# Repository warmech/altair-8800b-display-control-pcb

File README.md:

# Altair 8800B Display/Control PCB
This is a reproduction of the Altair 8800B Display/Control PCB, with some cleanup and reorganization of trace routing and pad placement. The 8800B’s D/C PCB, much like the original 8800’s front panel PCB, is the primary form of I/O for a stock machine: the LEDs for indicating the data/address/control signals and switches for setting the address and inputting data as well as controlling the CPU are to be found on this PCB. Unlike the original 8800, which drove the LEDs directly off the system bus, the 8800B D/C PCB buffers all signals and uses a 1702 EPROM (or just “PROM” as it would have originally been called) to pass control instructions off to the CPU.

This version of the D/C PCB is not a true 1:1 reproduction (just like the 8800B CPU and Interface cards), but strives to maintain a closely similar layout and trace routing to try to ensure that the hidden “feature” of the Altair remained present: the ability to generate EMI off the D/C board in such a fashion that music can be generated and received via an AM radio at very close proximity.

This design is presently untested and I am awaiting a set to be fabricated. Once I have tested this card in my 8800B, I will update this disclaimer to indicate as much. Until this disclaimer is updated and/or removed, this PCB is to be strictly treated as experimental only. User beware – these project and fabrication files are provided with absolutely zero guarantees.

For the accompanying CPU, Interface, and 1702-to-2716/32 adapter boards, please see the following repositories:

[Altair 8800B CPU Card](https://github.com/warmech/altair-8800b-cpu-card)

[Altair 8800B Interface Card](https://github.com/warmech/altair-8800b-interface-card)

[Altair 8800B 1702-to-2716/2732 Adapter](https://github.com/warmech/altair-8800b-1702-to-2716-eprom-adapter)

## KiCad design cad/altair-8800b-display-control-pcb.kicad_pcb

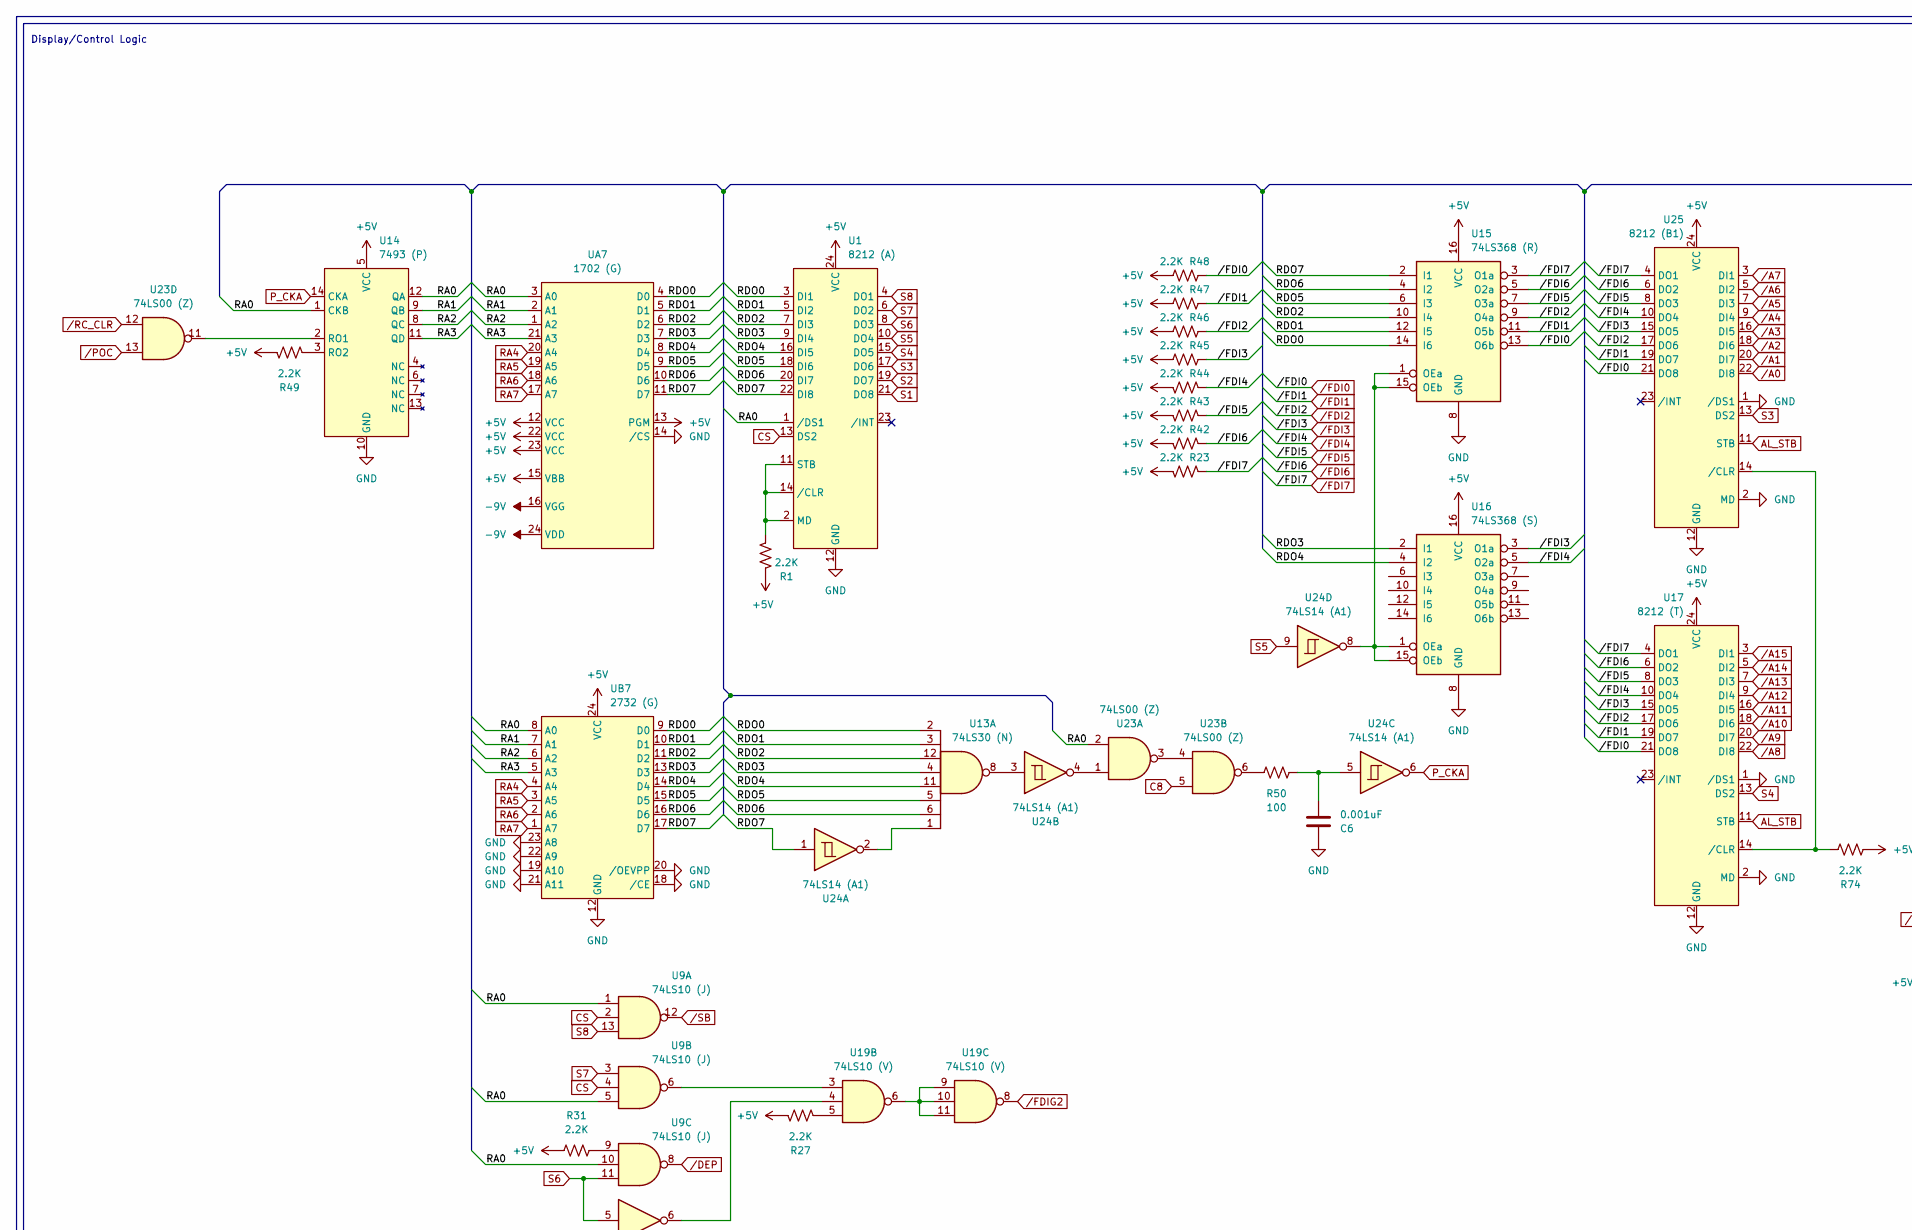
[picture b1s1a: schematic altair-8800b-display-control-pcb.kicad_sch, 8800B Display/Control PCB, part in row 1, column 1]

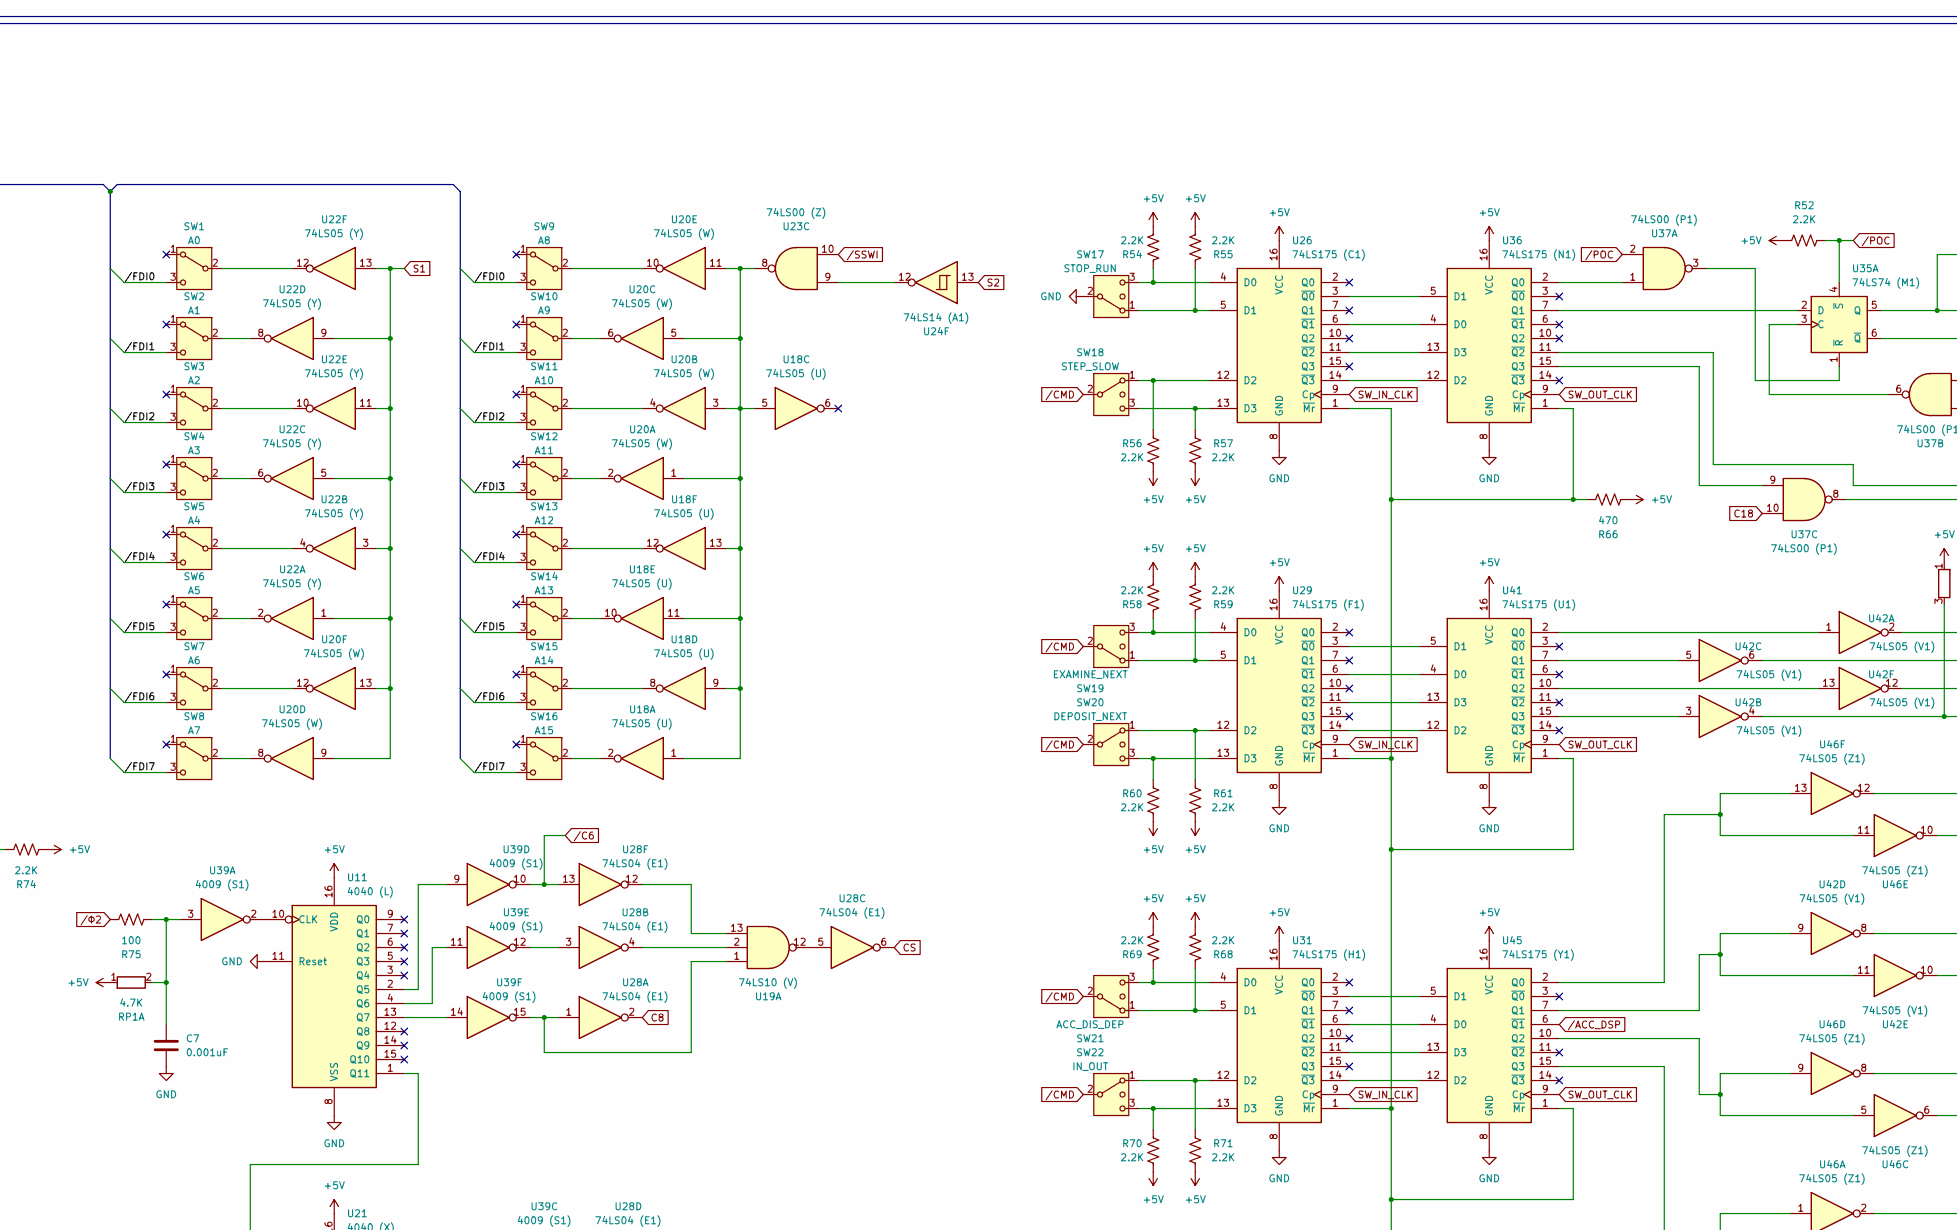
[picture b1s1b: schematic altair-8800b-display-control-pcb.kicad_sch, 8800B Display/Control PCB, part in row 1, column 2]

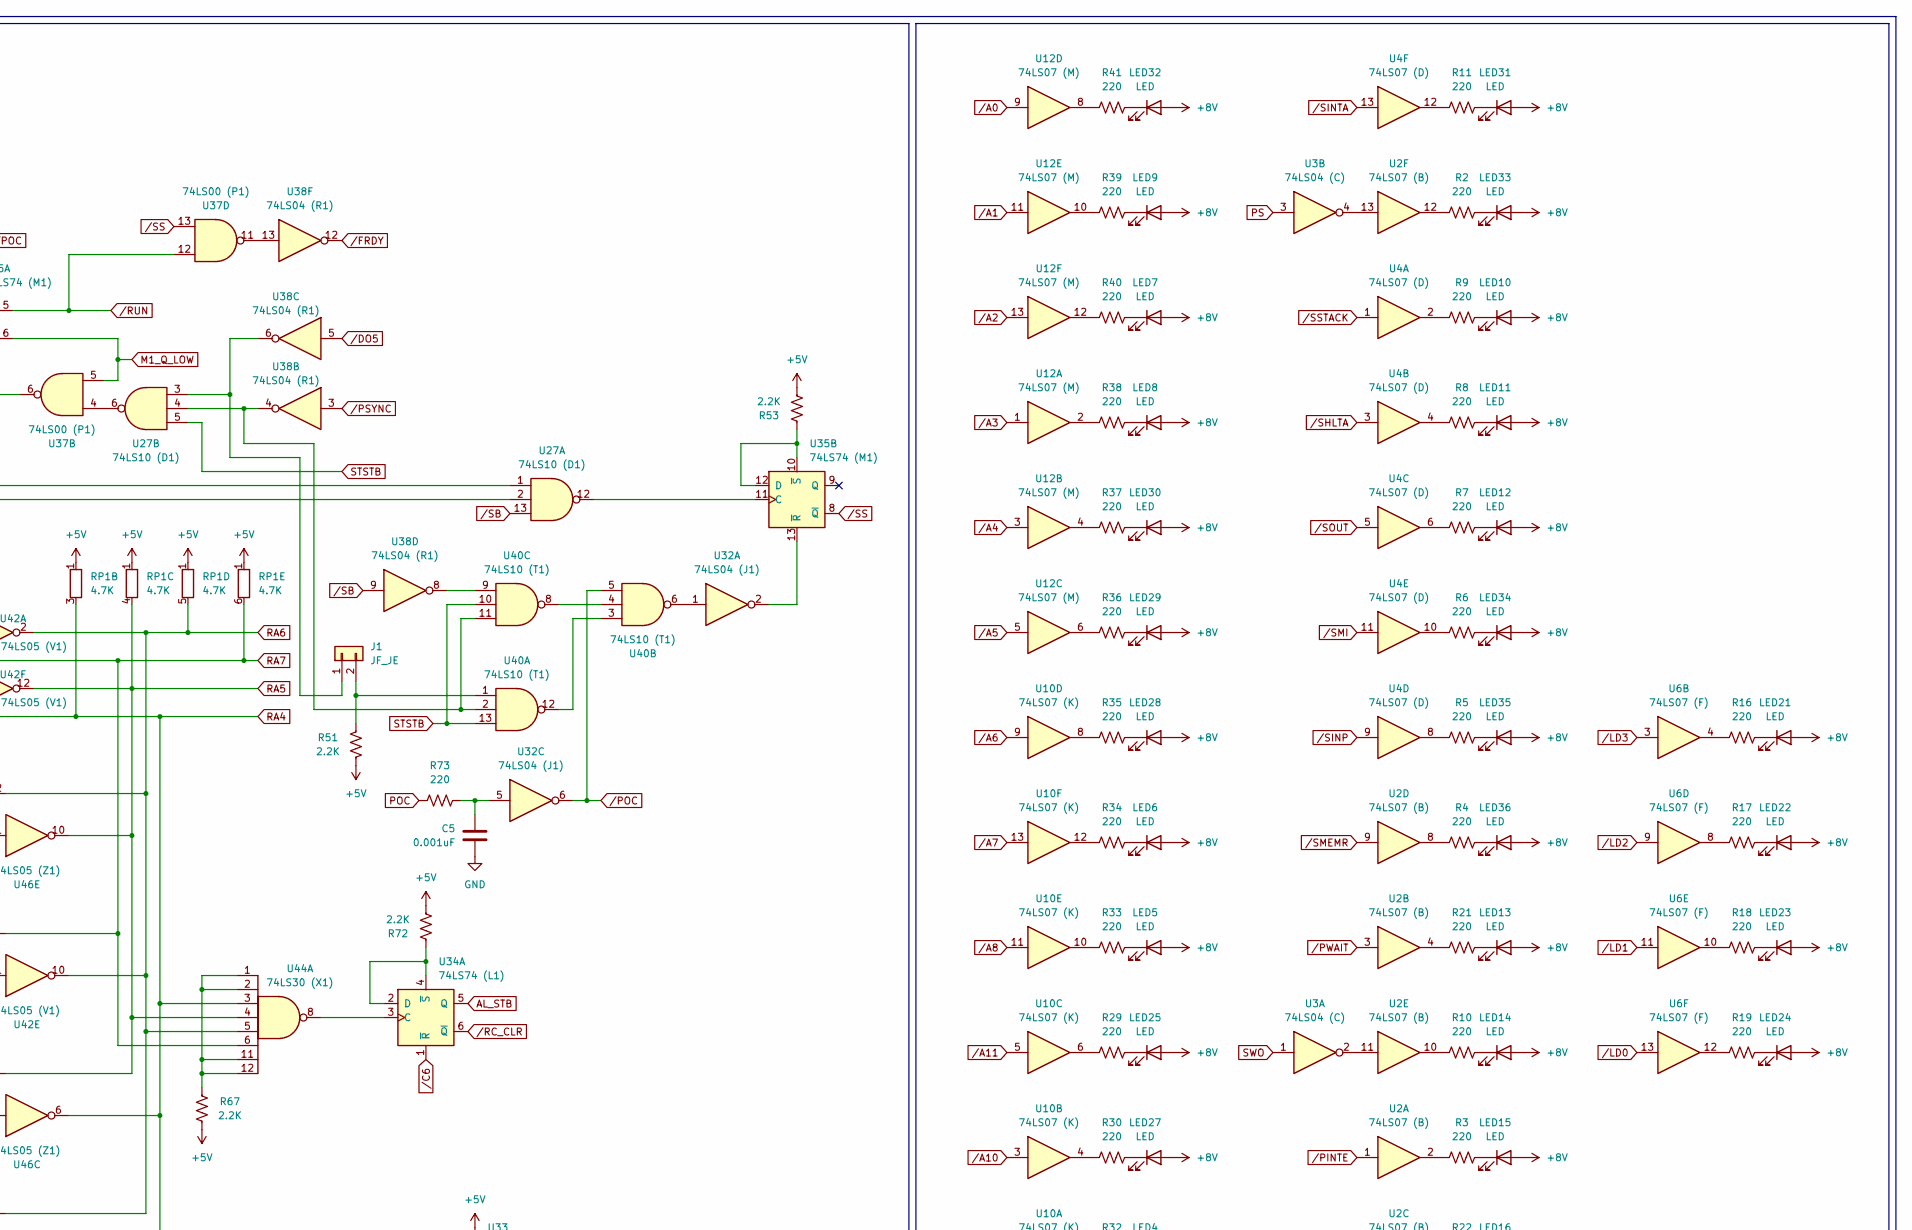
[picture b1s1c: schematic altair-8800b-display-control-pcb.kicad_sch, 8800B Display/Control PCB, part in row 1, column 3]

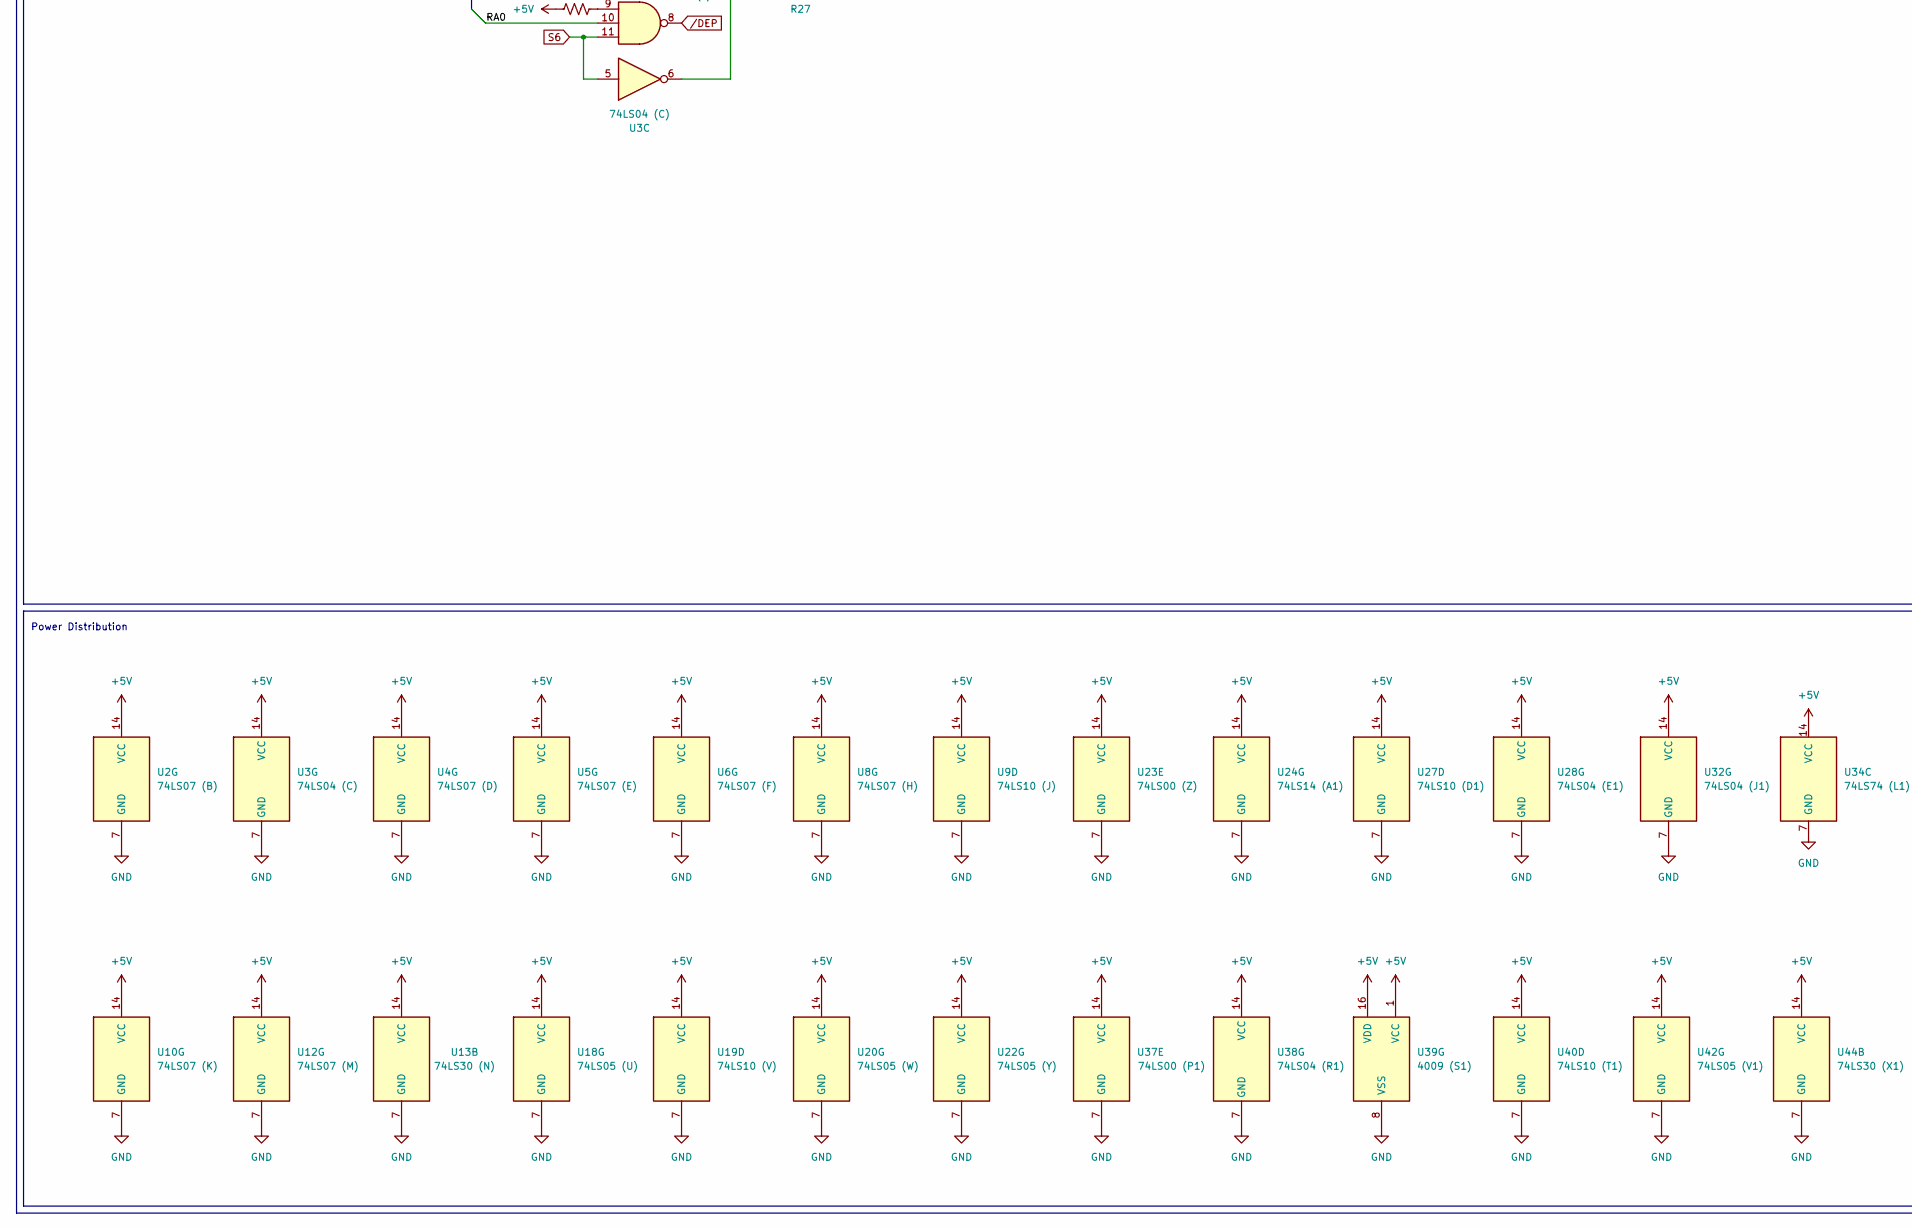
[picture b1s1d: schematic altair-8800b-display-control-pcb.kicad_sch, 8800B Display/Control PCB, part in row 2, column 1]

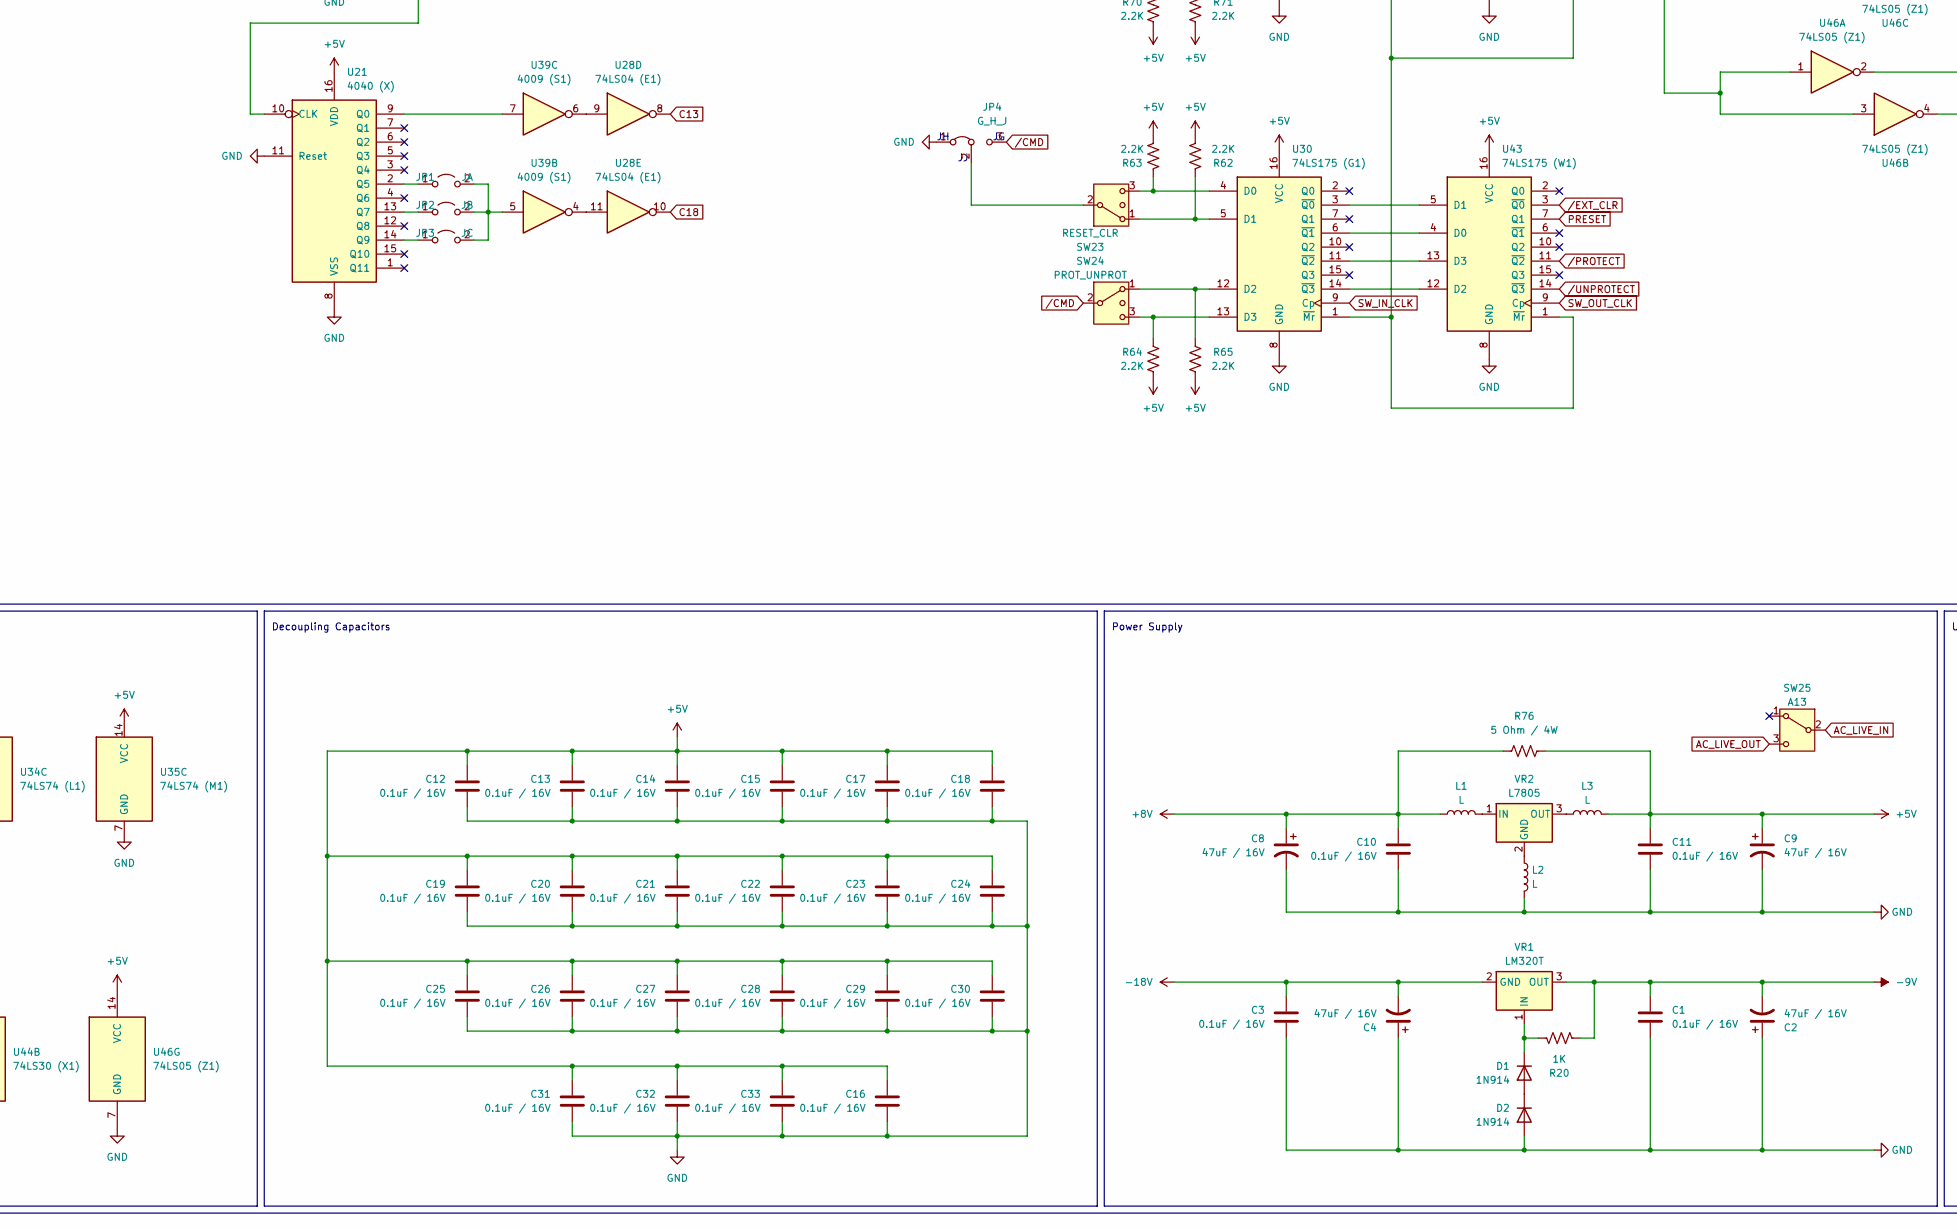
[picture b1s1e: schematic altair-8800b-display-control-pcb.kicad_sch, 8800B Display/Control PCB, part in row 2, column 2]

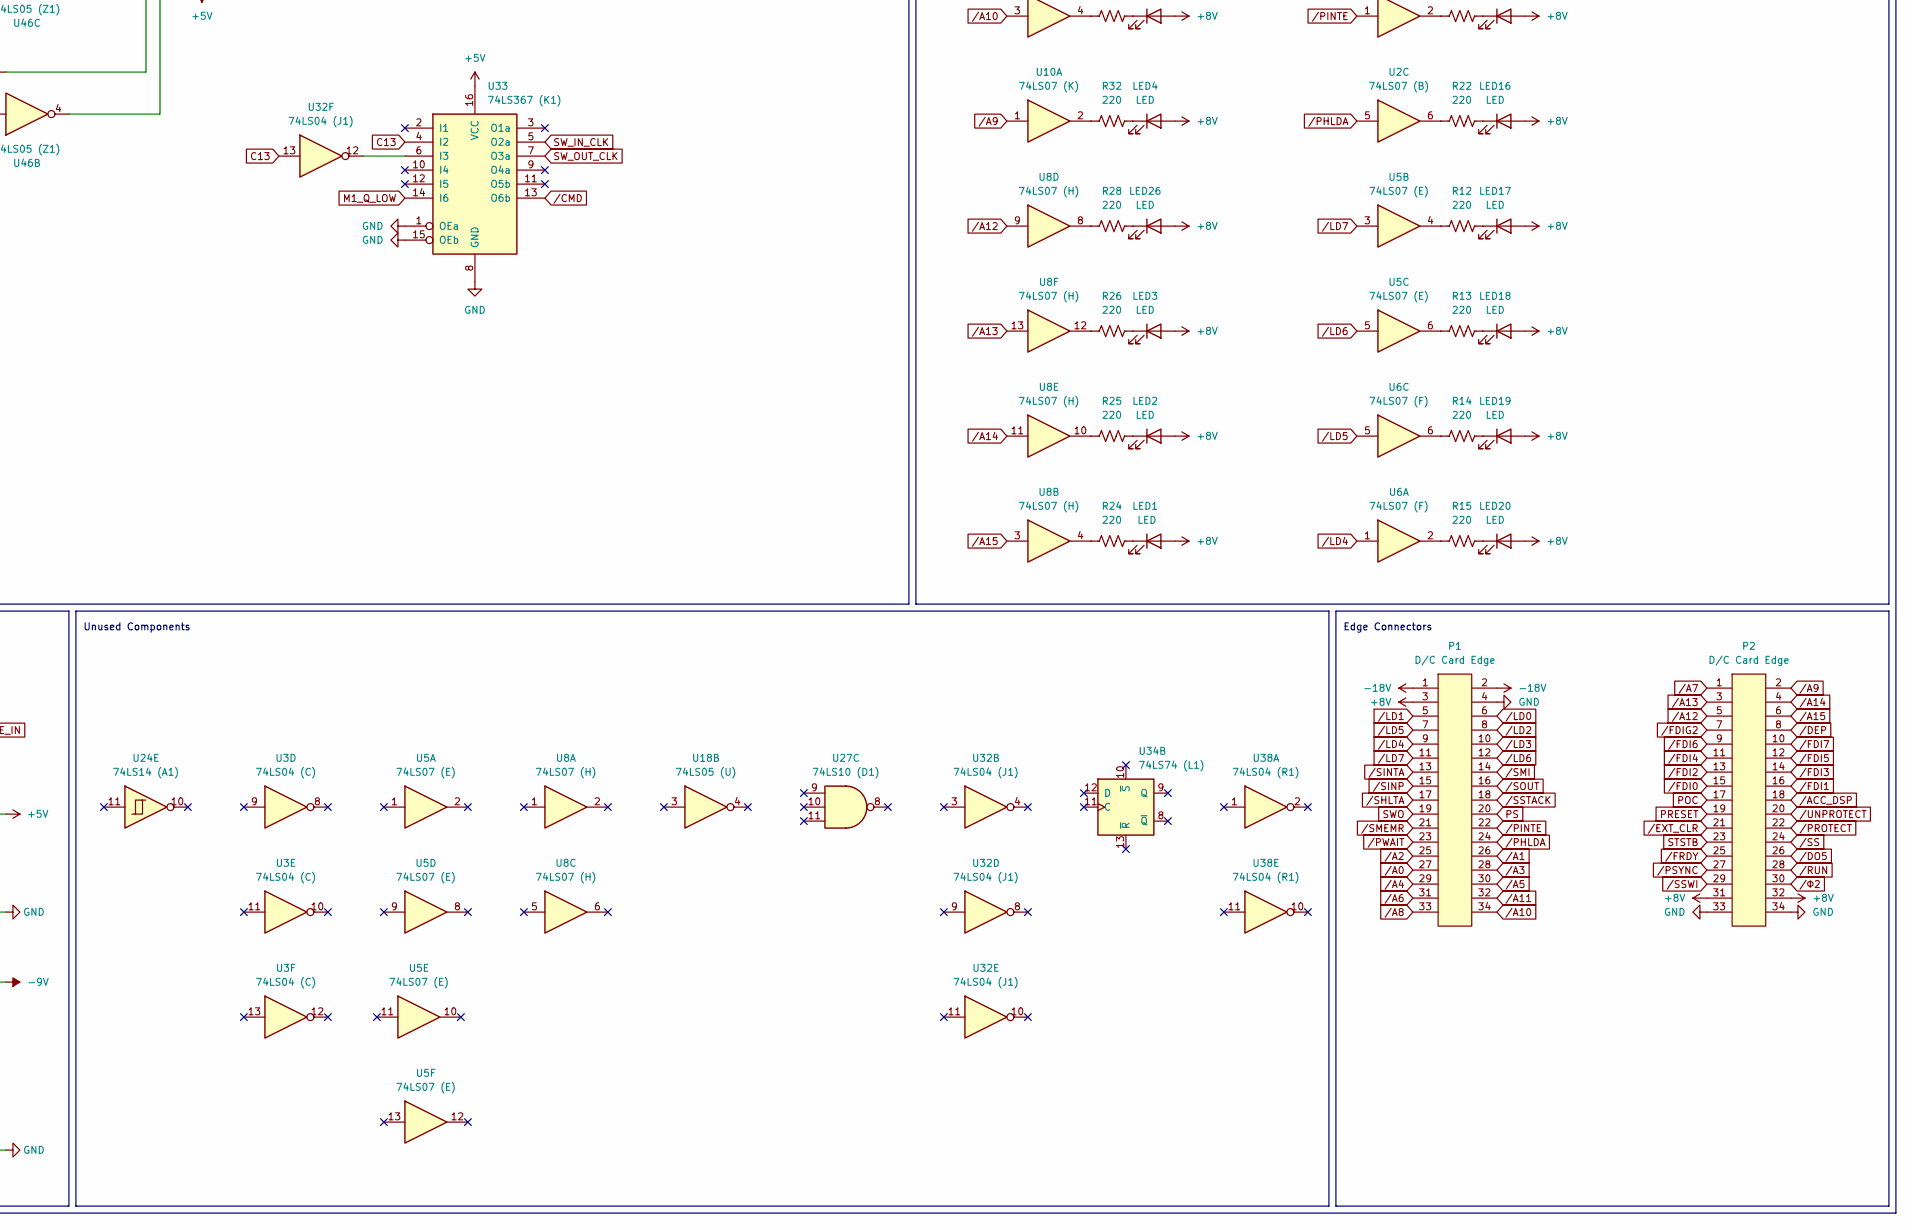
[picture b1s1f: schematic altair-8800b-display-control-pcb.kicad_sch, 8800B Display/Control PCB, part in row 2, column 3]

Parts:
C1, C3, C10, C11, C12, C13, C14, C15, C16, C17, C18, C19, C20, C21, C22, C23, C24, C25, C26, C27, C28, C29, C30, C31, C32, C33: 0.1uF / 16V; C_Disc_D7.0mm_W2.3mm_P5.00mm
C2, C4, C8, C9: 47uF / 16V; CP_Radial_Tantal_D4.5mm_P2.50mm
C5, C6, C7: 0.001uF; C_Disc_D7.0mm_W2.3mm_P5.00mm
D1, D2: 1N914; D_DO-35_SOD27_P7.62mm_Horizontal
J1: JF_JE; PinHeader_1x02_P2.54mm_Vertical
JP1: JA; PinHeader_1x02_P2.54mm_Vertical
JP2: JB; PinHeader_1x02_P2.54mm_Vertical
JP3: JC; PinHeader_1x02_P2.54mm_Vertical
JP4: G_H_J; PinHeader_1x03_P2.54mm_Vertical
L1, L2, L3: L; L_Axial_L5.3mm_D2.2mm_P7.62mm_Horizontal_Vishay_IM-1
LED1, LED2, LED3, LED4, LED5, LED6, LED7, LED8, LED9, LED10, LED11, LED12, LED13, LED14, LED15, LED16, LED17, LED18, LED19, LED20, LED21, LED22, LED23, LED24, LED25, LED26, LED27, LED28, LED29, LED30, LED31, LED32, LED33, LED34, LED35, LED36: LED; LED_D5.0mm
P1, P2: D/C Card Edge; Altair_8800B_Display_Control_Card_Edge
R1, R23, R27, R31, R42, R43, R44, R45, R46, R47, R48, R49, R51, R52, R53, R54, R55, R56, R57, R58, R59, R60, R61, R62, R63, R64, R65, R67, R68, R69, R70, R71, R72, R74: 2.2K; R_Axial_DIN0309_L9.0mm_D3.2mm_P12.70mm_Horizontal
R2, R3, R4, R5, R6, R7, R8, R9, R10, R11, R12, R13, R14, R15, R16, R17, R18, R19, R21, R22, R24, R25, R26, R28, R29, R30, R32, R33, R34, R35, R36, R37, R38, R39, R40, R41, R73: 220; R_Axial_DIN0309_L9.0mm_D3.2mm_P12.70mm_Horizontal
R20: 1K; R_Axial_DIN0309_L9.0mm_D3.2mm_P12.70mm_Horizontal
R50, R75: 100; R_Axial_DIN0309_L9.0mm_D3.2mm_P12.70mm_Horizontal
R66: 470; R_Axial_DIN0309_L9.0mm_D3.2mm_P12.70mm_Horizontal
R76: 5 Ohm / 4W; R_Axial_DIN0516_L15.5mm_D5.0mm_P30.48mm_Horizontal
RP1: 4.7K; R_Array_SIP6
SW1: A0; Altair_Toggle_Switch
SW2: A1; Altair_Toggle_Switch
SW3: A2; Altair_Toggle_Switch
SW4: A3; Altair_Toggle_Switch
SW5: A4; Altair_Toggle_Switch
SW6: A5; Altair_Toggle_Switch
SW7: A6; Altair_Toggle_Switch
SW8: A7; Altair_Toggle_Switch
SW9: A8; Altair_Toggle_Switch
SW10: A9; Altair_Toggle_Switch
SW11: A10; Altair_Toggle_Switch
SW12: A11; Altair_Toggle_Switch
SW13: A12; Altair_Toggle_Switch
SW14, SW25: A13; Altair_Toggle_Switch
SW15: A14; Altair_Toggle_Switch
SW16: A15; Altair_Toggle_Switch
SW17: STOP_RUN; Altair_Toggle_Switch_Momentary
SW18: STEP_SLOW; Altair_Toggle_Switch_Momentary
SW19: EXAMINE_NEXT; Altair_Toggle_Switch_Momentary
SW20: DEPOSIT_NEXT; Altair_Toggle_Switch_Momentary
SW21: ACC_DIS_DEP; Altair_Toggle_Switch_Momentary
SW22: IN_OUT; Altair_Toggle_Switch_Momentary
SW23: RESET_CLR; Altair_Toggle_Switch_Momentary
SW24: PROT_UNPROT; Altair_Toggle_Switch_Momentary
U1: 8212 (A); DIP-24_W15.24mm_LongPads
U2: 74LS07 (B); DIP-14_W7.62mm_LongPads
U3: 74LS04 (C); DIP-14_W7.62mm_LongPads
U4: 74LS07 (D); DIP-14_W7.62mm_LongPads
U5: 74LS07 (E); DIP-14_W7.62mm_LongPads
U6: 74LS07 (F); DIP-14_W7.62mm_LongPads
U8: 74LS07 (H); DIP-14_W7.62mm_LongPads
U9: 74LS10 (J); DIP-14_W7.62mm_LongPads
U10: 74LS07 (K); DIP-14_W7.62mm_LongPads
U11: 4040 (L); DIP-16_W7.62mm_LongPads
U12: 74LS07 (M); DIP-14_W7.62mm_LongPads
U13: 74LS30 (N); DIP-14_W7.62mm_LongPads
U14: 7493 (P); DIP-14_W7.62mm_LongPads
U15: 74LS368 (R); DIP-16_W7.62mm_LongPads
U16: 74LS368 (S); DIP-16_W7.62mm_LongPads
U17: 8212 (T); DIP-24_W15.24mm_LongPads
U18: 74LS05 (U); DIP-14_W7.62mm_LongPads
U19: 74LS10 (V); DIP-14_W7.62mm_LongPads
U20: 74LS05 (W); DIP-14_W7.62mm_LongPads
U21: 4040 (X); DIP-16_W7.62mm_LongPads
U22: 74LS05 (Y); DIP-14_W7.62mm_LongPads
U23: 74LS00 (Z); DIP-14_W7.62mm_LongPads
U24: 74LS14 (A1); DIP-14_W7.62mm_LongPads
U25: 8212 (B1); DIP-24_W15.24mm_LongPads
U26: 74LS175 (C1); DIP-16_W7.62mm_LongPads
U27: 74LS10 (D1); DIP-14_W7.62mm_LongPads
U28: 74LS04 (E1); DIP-14_W7.62mm_LongPads
U29: 74LS175 (F1); DIP-16_W7.62mm_LongPads
U30: 74LS175 (G1); DIP-16_W7.62mm_LongPads
U31: 74LS175 (H1); DIP-16_W7.62mm_LongPads
U32: 74LS04 (J1); DIP-14_W7.62mm_LongPads
U33: 74LS367 (K1); DIP-16_W7.62mm_LongPads
U34: 74LS74 (L1); DIP-14_W7.62mm_LongPads
U35: 74LS74 (M1); DIP-14_W7.62mm_LongPads
U36: 74LS175 (N1); DIP-16_W7.62mm_LongPads
U37: 74LS00 (P1); DIP-14_W7.62mm_LongPads
U38: 74LS04 (R1); DIP-14_W7.62mm_LongPads
U39: 4009 (S1); DIP-16_W7.62mm_LongPads
U40: 74LS10 (T1); DIP-14_W7.62mm_LongPads
U41: 74LS175 (U1); DIP-16_W7.62mm_LongPads
U42: 74LS05 (V1); DIP-14_W7.62mm_LongPads
U43: 74LS175 (W1); DIP-16_W7.62mm_LongPads
U44: 74LS30 (X1); DIP-14_W7.62mm_LongPads
U45: 74LS175 (Y1); DIP-16_W7.62mm_LongPads
U46: 74LS05 (Z1); DIP-14_W7.62mm_LongPads
UA7: 1702 (G); DIP-24_W15.24mm_LongPads
UB7: 2732 (G)
VR1: LM320T; TO-220-3_Horizontal_TabDown
VR2: L7805; TO-220-3_Horizontal_TabDown

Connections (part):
+5V: C9.1, C11.1, C12.1, C13.1, C14.1, C15.1, C16.1, C17.1, C18.1, C19.1, C20.1, C21.1, C22.1, C23.1, C24.1, C25.1, C26.1, C27.1, C28.1, C29.1, C30.1, C31.1, C32.1, C33.1, L3.2, R1.1, R23.1, R27.1, R31.1, R42.1, R43.1, R44.1, R45.2, R46.2, R47.2, R48.2, R49.1, R51.2, R52.1, R53.2, R54.1, R55.2, R56.1, R57.2, R58.1, R59.2, R60.1, R61.2, R62.2, R63.1, R64.1, R65.2, R66.1, R67.2, R68.2, R69.1, R70.1, R71.2, R72.2, R74.1, R76.2, RP1.1 (R1), U1.24 (VCC), U2.14 (VCC), U3.14 (VCC), U4.14 (VCC), U5.14 (VCC), U6.14 (VCC), U8.14 (VCC), U9.14 (VCC), U10.14 (VCC), U11.16 (VDD), U12.14 (VCC), U13.14 (VCC), U14.5 (VCC), U15.16 (VCC), U16.16 (VCC), U17.24 (VCC), U18.14 (VCC), U19.14 (VCC), U20.14 (VCC), U21.16 (VDD), U22.14 (VCC)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
+8V: C8.1, C10.1, L1.1, LED1.2 (A), LED2.2 (A), LED3.2 (A), LED4.2 (A), LED5.2 (A), LED6.2 (A), LED7.2 (A), LED8.2 (A), LED9.2 (A), LED10.2 (A), LED11.2 (A), LED12.2 (A), LED13.2 (A), LED14.2 (A), LED15.2 (A), LED16.2 (A), LED17.2 (A), LED18.2 (A), LED19.2 (A), LED20.2 (A), LED21.2 (A), LED22.2 (A), LED23.2 (A), LED24.2 (A), LED25.2 (A), LED26.2 (A), LED27.2 (A), LED28.2 (A), LED29.2 (A), LED30.2 (A), LED31.2 (A), LED32.2 (A), LED33.2 (A), LED34.2 (A), LED35.2 (A), LED36.2 (A), P1.3, P2.31, P2.32, R76.1
-9V: C1.1, C2.2, R20.2, UA7.16 (VGG), UA7.24 (VDD), VR1.3 (OUT)
-18V: C3.1, C4.2, P1.1, P1.2, VR1.2 (GND)
/RA0: U1.1 (/DS1), U9.1, U9.5, U9.10, U14.1 (CKB), U14.12 (QA), U23.2, UA7.3 (A0), UB7.8 (A0)
/RA1: U14.9 (QB), UA7.2 (A1), UB7.7 (A1)
/RA2: U14.8 (QC), UA7.1 (A2), UB7.6 (A2)
/RA3: U14.11 (QD), UA7.21 (A3), UB7.5 (A3)
/RDO0: U1.3 (DI1), U13.2, U15.14 (I6), UA7.4 (D0), UB7.9 (D0)
/RDO1: U1.5 (DI2), U13.3, U15.12 (I5), UA7.5 (D1), UB7.10 (D1)
/RDO2: U1.7 (DI3), U13.12, U15.10 (I4), UA7.6 (D2), UB7.11 (D2)
/RDO3: U1.9 (DI4), U13.4, U16.2 (I1), UA7.7 (D3), UB7.13 (D3)
/RDO4: U1.16 (DI5), U13.11, U16.4 (I2), UA7.8 (D4), UB7.14 (D4)
/RDO5: U1.18 (DI6), U13.5, U15.6 (I3), UA7.9 (D5), UB7.15 (D5)
/RDO6: U1.20 (DI7), U13.6, U15.4 (I2), UA7.10 (D6), UB7.16 (D6)
/RDO7: U1.22 (DI8), U15.2 (I1), U24.1, UA7.11 (D7), UB7.17 (D7)
AC_LIVE_IN: SW25.2 (B)
AC_LIVE_OUT: SW25.3 (C)
AL_STB: U17.11 (STB), U25.11 (STB), U34.5 (Q)
C8: U23.5, U28.2
C13: U28.8, U32.13, U33.4 (I2)
C18: U28.10, U37.10
CS: U1.13 (DS2), U9.2, U9.4, U28.6
GND: C1.2, C2.1, C3.2, C4.1, C5.1, C6.1, C7.1, C8.2, C9.2, C10.2, C11.2, C12.2, C13.2, C14.2, C15.2, C16.2, C17.2, C18.2, C19.2, C20.2, C21.2, C22.2, C23.2, C24.2, C25.2, C26.2, C27.2, C28.2, C29.2, C30.2, C31.2, C32.2, C33.2, D2.2 (A), JP4.1 (A), L2.2, P1.4, P2.33, P2.34, SW17.2 (3), U1.12 (GND), U2.7 (GND), U3.7 (GND), U4.7 (GND), U5.7 (GND), U6.7 (GND), U8.7 (GND), U9.7 (GND), U10.7 (GND), U11.8 (VSS), U11.11 (Reset), U12.7 (GND), U13.7 (GND), U14.10 (GND), U15.8 (GND), U16.8 (GND), U17.1 (/DS1), U17.2 (MD), U17.12 (GND), U18.7 (GND), U19.7 (GND), U20.7 (GND), U21.8 (VSS), U21.11 (Reset), U22.7 (GND), U23.7 (GND), U24.7 (GND), U25.1 (/DS1), U25.2 (MD), U25.12 (GND), U26.8 (GND), U27.7 (GND), U28.7 (GND), U29.8 (GND), U30.8 (GND), U31.8 (GND), U32.7 (GND), U33.1 (OEa), U33.8 (GND), U33.15 (OEb), U34.7 (GND), U35.7 (GND), U36.8 (GND)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
M1_Q_LOW: U33.14 (I6), U35.6 (~Q), U37.5
unnamed: C5.2, R73.2, U32.5
unnamed: C6.2, R50.2, U24.5
unnamed: D1.2 (A), D2.1 (K)
unnamed: D1.1 (K), R20.1, VR1.1 (IN)
unnamed: J1.1, U27.3, U38.6
unnamed: J1.2, R51.1, U40.1
unnamed: JP1.1 (A), U21.2 (Q5)
unnamed: JP1.2 (B), JP2.2 (B), JP3.2 (B), U39.5
unnamed: JP2.1 (A), U21.13 (Q7)
unnamed: JP3.1 (A), U21.14 (Q9)
unnamed: JP4.2 (C), SW23.2 (3)
unnamed: LED1.1 (K), R24.2
unnamed: LED2.1 (K), R25.2
unnamed: LED3.1 (K), R26.2
unnamed: LED4.1 (K), R32.2
unnamed: LED5.1 (K), R33.2
unnamed: LED6.1 (K), R34.2
unnamed: LED7.1 (K), R40.2
unnamed: LED8.1 (K), R38.2
unnamed: LED9.1 (K), R39.2
unnamed: LED10.1 (K), R9.2
unnamed: LED11.1 (K), R8.2
unnamed: LED12.1 (K), R7.2
unnamed: LED13.1 (K), R21.2
unnamed: LED14.1 (K), R10.2
unnamed: LED15.1 (K), R3.2
unnamed: LED16.1 (K), R22.2
unnamed: LED17.1 (K), R12.2
unnamed: LED18.1 (K), R13.2
unnamed: LED19.1 (K), R14.2
unnamed: LED20.1 (K), R15.2
unnamed: LED21.1 (K), R16.2
unnamed: LED22.1 (K), R17.2
unnamed: LED23.1 (K), R18.2
unnamed: LED24.1 (K), R19.2
unnamed: LED25.1 (K), R29.2
unnamed: LED26.1 (K), R28.2
unnamed: LED27.1 (K), R30.2
unnamed: LED28.1 (K), R35.2
unnamed: LED29.1 (K), R36.2
unnamed: LED30.1 (K), R37.2
unnamed: LED31.1 (K), R11.2
unnamed: LED32.1 (K), R41.2
unnamed: LED33.1 (K), R2.2
unnamed: LED34.1 (K), R6.2
unnamed: LED35.1 (K), R5.2
unnamed: LED36.1 (K), R4.2
unnamed: R2.1, U2.12
unnamed: R3.1, U2.2
unnamed: R4.1, U2.8
unnamed: R5.1, U4.8
unnamed: R6.1, U4.10
unnamed: R7.1, U4.6
unnamed: R8.1, U4.4
unnamed: R9.1, U4.2
unnamed: R10.1, U2.10
unnamed: R11.1, U4.12
unnamed: R12.1, U5.4
unnamed: R13.1, U5.6
unnamed: R14.1, U6.6
unnamed: R15.1, U6.2
unnamed: R16.1, U6.4
unnamed: R17.1, U6.8
unnamed: R18.1, U6.10
unnamed: R19.1, U6.12
unnamed: R21.1, U2.4
unnamed: R22.1, U2.6
unnamed: R24.1, U8.4
unnamed: R25.1, U8.10
unnamed: R26.1, U8.12
unnamed: R27.2, U19.5
unnamed: R28.1, U8.8
unnamed: R29.1, U10.6
unnamed: R30.1, U10.4
unnamed: R31.2, U9.9
unnamed: R32.1, U10.2
unnamed: R33.1, U10.10
unnamed: R34.1, U10.12
unnamed: R35.1, U10.8
unnamed: R36.1, U12.6
unnamed: R37.1, U12.4
unnamed: R38.1, U12.2
unnamed: R39.1, U12.10
unnamed: R40.1, U12.12
unnamed: R41.1, U12.8
unnamed: R50.1, U23.6
unnamed: R67.1, U44.1, U44.2, U44.11, U44.12
unnamed: C7.2, R75.1, RP1.2 (R1.2), U39.3
unnamed: SW1.2 (B), U22.12
unnamed: SW2.2 (B), U22.8
unnamed: SW3.2 (B), U22.10
unnamed: SW4.2 (B), U22.6
unnamed: SW5.2 (B), U22.4
unnamed: SW6.2 (B), U22.2
unnamed: SW7.2 (B), U20.12
unnamed: SW8.2 (B), U20.8
unnamed: SW9.2 (B), U20.10
unnamed: SW10.2 (B), U20.6
unnamed: SW11.2 (B), U20.4
unnamed: SW12.2 (B), U20.2
unnamed: SW13.2 (B), U18.12
unnamed: SW14.2 (B), U18.10
unnamed: SW15.2 (B), U18.8
unnamed: SW16.2 (B), U18.2
unnamed: R54.2, SW17.3 (4), U26.4 (D0)
unnamed: R57.1, SW18.3 (4), U26.13 (D3)
unnamed: R58.2, SW19.3 (4), U29.4 (D0)
unnamed: R60.2, SW20.3 (4), U29.13 (D3)
unnamed: R69.2, SW21.3 (4), U31.4 (D0)
unnamed: R70.2, SW22.3 (4), U31.13 (D3)
unnamed: R63.2, SW23.3 (4), U30.4 (D0)
unnamed: R64.2, SW24.3 (4), U30.13 (D3)
unnamed: R1.2, U1.2 (MD), U1.11 (STB), U1.14 (/CLR)
unnamed: U2.11, U3.2
unnamed: U2.13, U3.4
unnamed: U11.10 (CLK), U39.2
unnamed: U11.2 (Q5), U39.9
unnamed: U11.4 (Q6), U39.11
unnamed: U11.13 (Q7), U39.14
unnamed: U11.1 (Q11), U21.10 (CLK)
unnamed: U13.1, U24.2
unnamed: U13.8, U24.3
unnamed: U14.2 (RO1), U23.11
unnamed: R49.2, U14.3 (RO2)
unnamed: U15.1 (OEa), U15.15 (OEb), U16.1 (OEa), U16.15 (OEb), U24.8
unnamed: R74.2, U17.14 (/CLR), U25.14 (/CLR)
unnamed: U18.1, U18.5, U18.9, U18.11, U18.13, U20.1, U20.3, U20.5, U20.11, U23.8
unnamed: U19.1, U28.1, U39.15
unnamed: U19.2, U28.4
unnamed: U9.6, U19.3
unnamed: U3.6, U19.4
unnamed: U19.6, U19.9, U19.10, U19.11
unnamed: U19.12, U28.5
unnamed: U19.13, U28.12
unnamed: U21.9 (Q0), U39.7
unnamed: U23.1, U24.4
unnamed: U23.3, U23.4
unnamed: U23.9, U24.12
unnamed: R55.1, SW17.1, U26.5 (D1)
unnamed: R56.2, SW18.1, U26.12 (D2)
unnamed: R66.2, U26.1 (~Mr), U29.1 (~Mr), U30.1 (~Mr), U31.1 (~Mr), U36.1 (~Mr), U41.1 (~Mr), U43.1 (~Mr), U45.1 (~Mr)
unnamed: U26.3 (~Q0), U36.5 (D1)
unnamed: U26.6 (~Q1), U36.4 (D0)
unnamed: U26.11 (~Q2), U36.13 (D3)
unnamed: U26.14 (~Q3), U36.12 (D2)
unnamed: U27.2, U37.8
unnamed: U27.4, U38.4, U40.2, U40.11
unnamed: U27.6, U37.4
unnamed: U28.3, U39.12
unnamed: U28.9, U39.6
unnamed: U28.11, U39.4
unnamed: R59.1, SW19.1, U29.5 (D1)
unnamed: R61.1, SW20.1, U29.12 (D2)
unnamed: U29.3 (~Q0), U41.5 (D1)
unnamed: U29.6 (~Q1), U41.4 (D0)
unnamed: U29.11 (~Q2), U41.13 (D3)
unnamed: U29.14 (~Q3), U41.12 (D2)
unnamed: R62.1, SW23.1, U30.5 (D1)
unnamed: R65.1, SW24.1, U30.12 (D2)
unnamed: U30.3 (~Q0), U43.5 (D1)
unnamed: U30.6 (~Q1), U43.4 (D0)
unnamed: U30.11 (~Q2), U43.13 (D3)
unnamed: U30.14 (~Q3), U43.12 (D2)
unnamed: R68.1, SW21.1, U31.5 (D1)
unnamed: R71.1, SW22.1, U31.12 (D2)
unnamed: U31.3 (~Q0), U45.5 (D1)
unnamed: U31.6 (~Q1), U45.4 (D0)
unnamed: U31.11 (~Q2), U45.13 (D3)
unnamed: U31.14 (~Q3), U45.12 (D2)
unnamed: U32.1, U40.6
unnamed: U32.12, U33.6 (I3)
unnamed: U34.3 (C), U44.8
unnamed: R72.1, U34.2 (D), U34.4 (~S)
unnamed: U35.3 (C), U37.6
unnamed: U35.2 (D), U36.7 (Q1)
unnamed: U35.1 (~R), U37.3
unnamed: U27.12, U35.11 (C)
unnamed: R53.1, U35.10 (~S), U35.12 (D)
unnamed: U32.2, U35.13 (~R)
unnamed: U36.2 (Q0), U37.1
unnamed: U36.15 (Q3), U37.9
unnamed: U27.1, U36.11 (~Q2)
unnamed: U37.11, U38.13
unnamed: U38.8, U40.9
unnamed: U40.4, U40.8
unnamed: U40.3, U40.12
unnamed: U41.2 (Q0), U42.1
unnamed: U41.7 (Q1), U42.5
unnamed: U41.10 (Q2), U42.13
unnamed: U41.15 (Q3), U42.3
unnamed: U45.2 (Q0), U46.11, U46.13
unnamed: U42.9, U42.11, U45.7 (Q1)
unnamed: U45.10 (Q2), U46.5, U46.9
unnamed: U45.15 (Q3), U46.1, U46.3
unnamed: L2.1, VR2.2 (GND)
unnamed: L1.2, VR2.1 (IN)
unnamed: L3.1, VR2.3 (OUT)
POC: P2.17, R73.1
PRESET: P2.19, U43.7 (Q1)
PS: P1.20, U3.3
P_CKA: U14.14 (CKA), U24.6
RA4: RP1.3 (R2.2), U42.4, U44.3, U46.4, U46.6, UA7.20 (A4), UB7.4 (A4)
RA5: RP1.4 (R3.2), U42.12, U44.4, U46.8, U46.10, UA7.19 (A5), UB7.3 (A5)
RA6: RP1.5 (R4.2), U42.2, U42.10, U44.5, U46.2, U46.12, UA7.18 (A6), UB7.2 (A6)
RA7: RP1.6 (R5.2), U42.6, U42.8, U44.6, UA7.17 (A7), UB7.1 (A7)
S1: U1.21 (DO8), U20.9, U20.13, U22.1, U22.3, U22.5, U22.9, U22.11, U22.13
S2: U1.19 (DO7), U24.13
S3: U1.17 (DO6), U25.13 (DS2)
S4: U1.15 (DO5), U17.13 (DS2)
S5: U1.10 (DO4), U24.9
S6: U1.8 (DO3), U3.5, U9.11
S7: U1.6 (DO2), U9.3
S8: U1.4 (DO1), U9.13
STSTB: P2.23, U27.5, U40.10, U40.13
SWO: P1.19, U3.1
SW_IN_CLK: U26.9 (Cp), U29.9 (Cp), U30.9 (Cp), U31.9 (Cp), U33.5 (O2a)
SW_OUT_CLK: U33.7 (O3a), U36.9 (Cp), U41.9 (Cp), U43.9 (Cp), U45.9 (Cp)
/A0: P1.27, U12.9, U25.22 (DI8)
/A1: P1.26, U12.11, U25.20 (DI7)
/A2: P1.25, U12.13, U25.18 (DI6)
/A3: P1.28, U12.1, U25.16 (DI5)
/A4: P1.29, U12.3, U25.9 (DI4)
/A5: P1.30, U12.5, U25.7 (DI3)
/A6: P1.31, U10.9, U25.5 (DI2)
/A7: P2.1, U10.13, U25.3 (DI1)
/A8: P1.33, U10.11, U17.22 (DI8)
/A9: P2.2, U10.1, U17.20 (DI7)
/A10: P1.34, U10.3, U17.18 (DI6)
/A11: P1.32, U10.5, U17.16 (DI5)
/A12: P2.5, U8.9, U17.9 (DI4)
/A13: P2.3, U8.13, U17.7 (DI3)
/A14: P2.4, U8.11, U17.5 (DI2)
/A15: P2.6, U8.3, U17.3 (DI1)
/ACC_DSP: P2.18, U45.6 (~Q1)
/C6: U28.13, U34.1 (~R), U39.10
/CMD: JP4.3 (B), SW18.2 (3), SW19.2 (3), SW20.2 (3), SW21.2 (3), SW22.2 (3), SW24.2 (3), U33.13 (O6b)
/DEP: P2.8, U9.8
/DO5: P2.26, U38.5
/EXT_CLR: P2.21, U43.3 (~Q0)
/FDI0: P2.15, R48.1, SW1.3 (C), SW9.3 (C), U15.13 (O6b), U17.21 (DO8), U25.21 (DO8)
/FDI1: P2.16, R47.1, SW2.3 (C), SW10.3 (C), U15.11 (O5b), U17.19 (DO7), U25.19 (DO7)
/FDI2: P2.13, R46.1, SW3.3 (C), SW11.3 (C), U15.9 (O4a), U17.17 (DO6), U25.17 (DO6)
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
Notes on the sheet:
Power Distribution
Power Supply
Unused Components
Edge Connectors
Display/Control Logic
Decoupling Capacitors

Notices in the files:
cad/altair-8800b-display-control-pcb.kicad_pcb:
© 1976
